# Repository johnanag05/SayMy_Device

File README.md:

# SayMy_Device

A simple 3-key macropad for playing Geometry Dah and OSU!

---

## Screenshots

### Schematic

### PCB

### Case

---

## Bill of Materials (BOM)

| Part | Quantity |
|------|----------|
| Cherry MX Switches | 3 |
| DSA Keycaps | 3 |
| Seeeduino XIAO | 1 |
| PCB | 1 | 
| M3x16mm screws | 4 |
| M3x5x4 Heatset inserts | 4 |
| EC11 Rotary encoder | 1 |
---

## Firmware

Built with QMK firmware

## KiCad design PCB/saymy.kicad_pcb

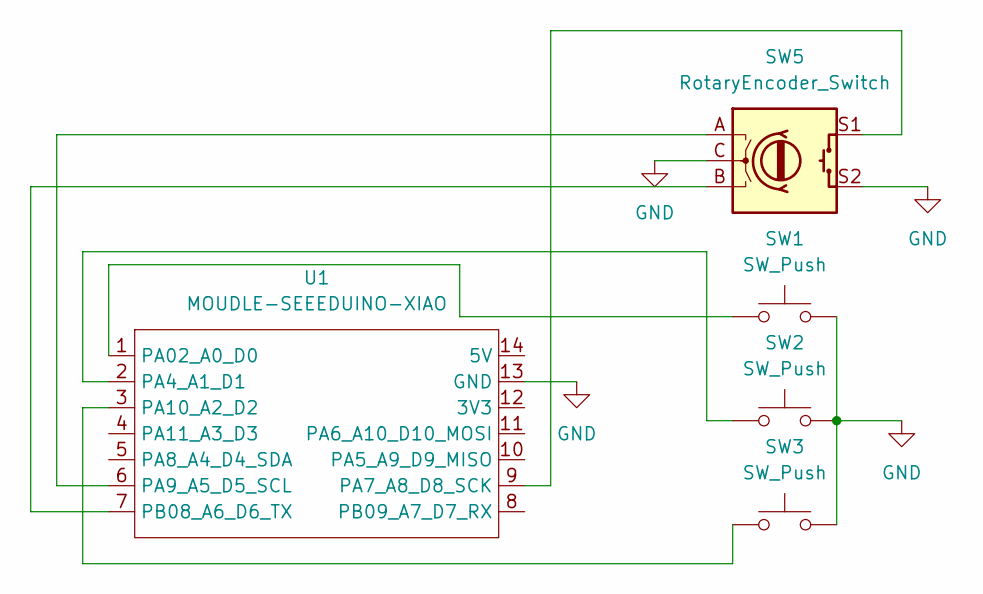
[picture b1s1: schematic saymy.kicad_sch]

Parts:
SW1, SW2, SW3: SW_Push; SW_Cherry_MX_1.00u_PCB
SW5: RotaryEncoder_Switch; RotaryEncoder_Alps_EC11E-Switch_Vertical_H20mm
U1: MOUDLE-SEEEDUINO-XIAO; XIAO-Generic-Hybrid-14P-2.54-21X17.8MM

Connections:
GND: SW1.2, SW2.2, SW3.2, SW5.C, SW5.S2, U1.13 (GND)
unnamed: SW1.1, U1.1 (PA02_A0_D0)
unnamed: SW2.1, U1.2 (PA4_A1_D1)
unnamed: SW5.S1, U1.9 (PA7_A8_D8_SCK)
unnamed: SW5.A, U1.6 (PA9_A5_D5_SCL)
unnamed: SW3.1, U1.3 (PA10_A2_D2)
unnamed: SW5.B, U1.7 (PB08_A6_D6_TX)

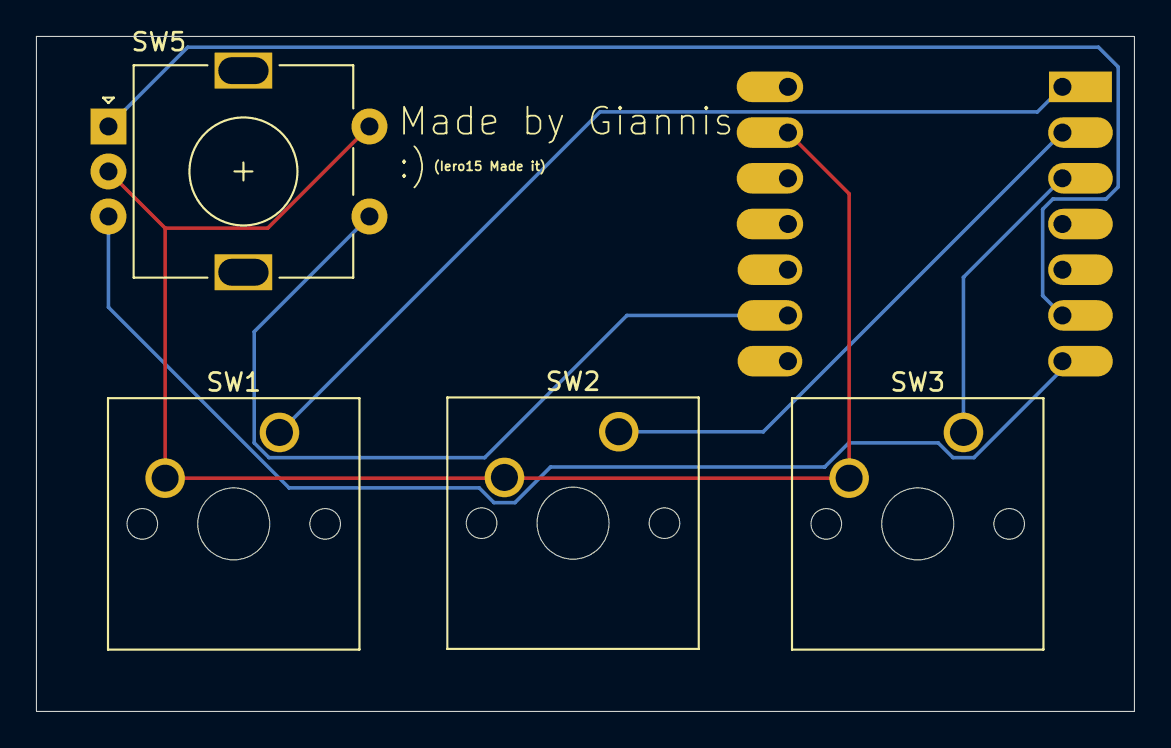
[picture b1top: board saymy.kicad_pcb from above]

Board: 2 copper layers, 61.0 x 37.5 mm, 5 parts (1 on the bottom side), 7 nets.
